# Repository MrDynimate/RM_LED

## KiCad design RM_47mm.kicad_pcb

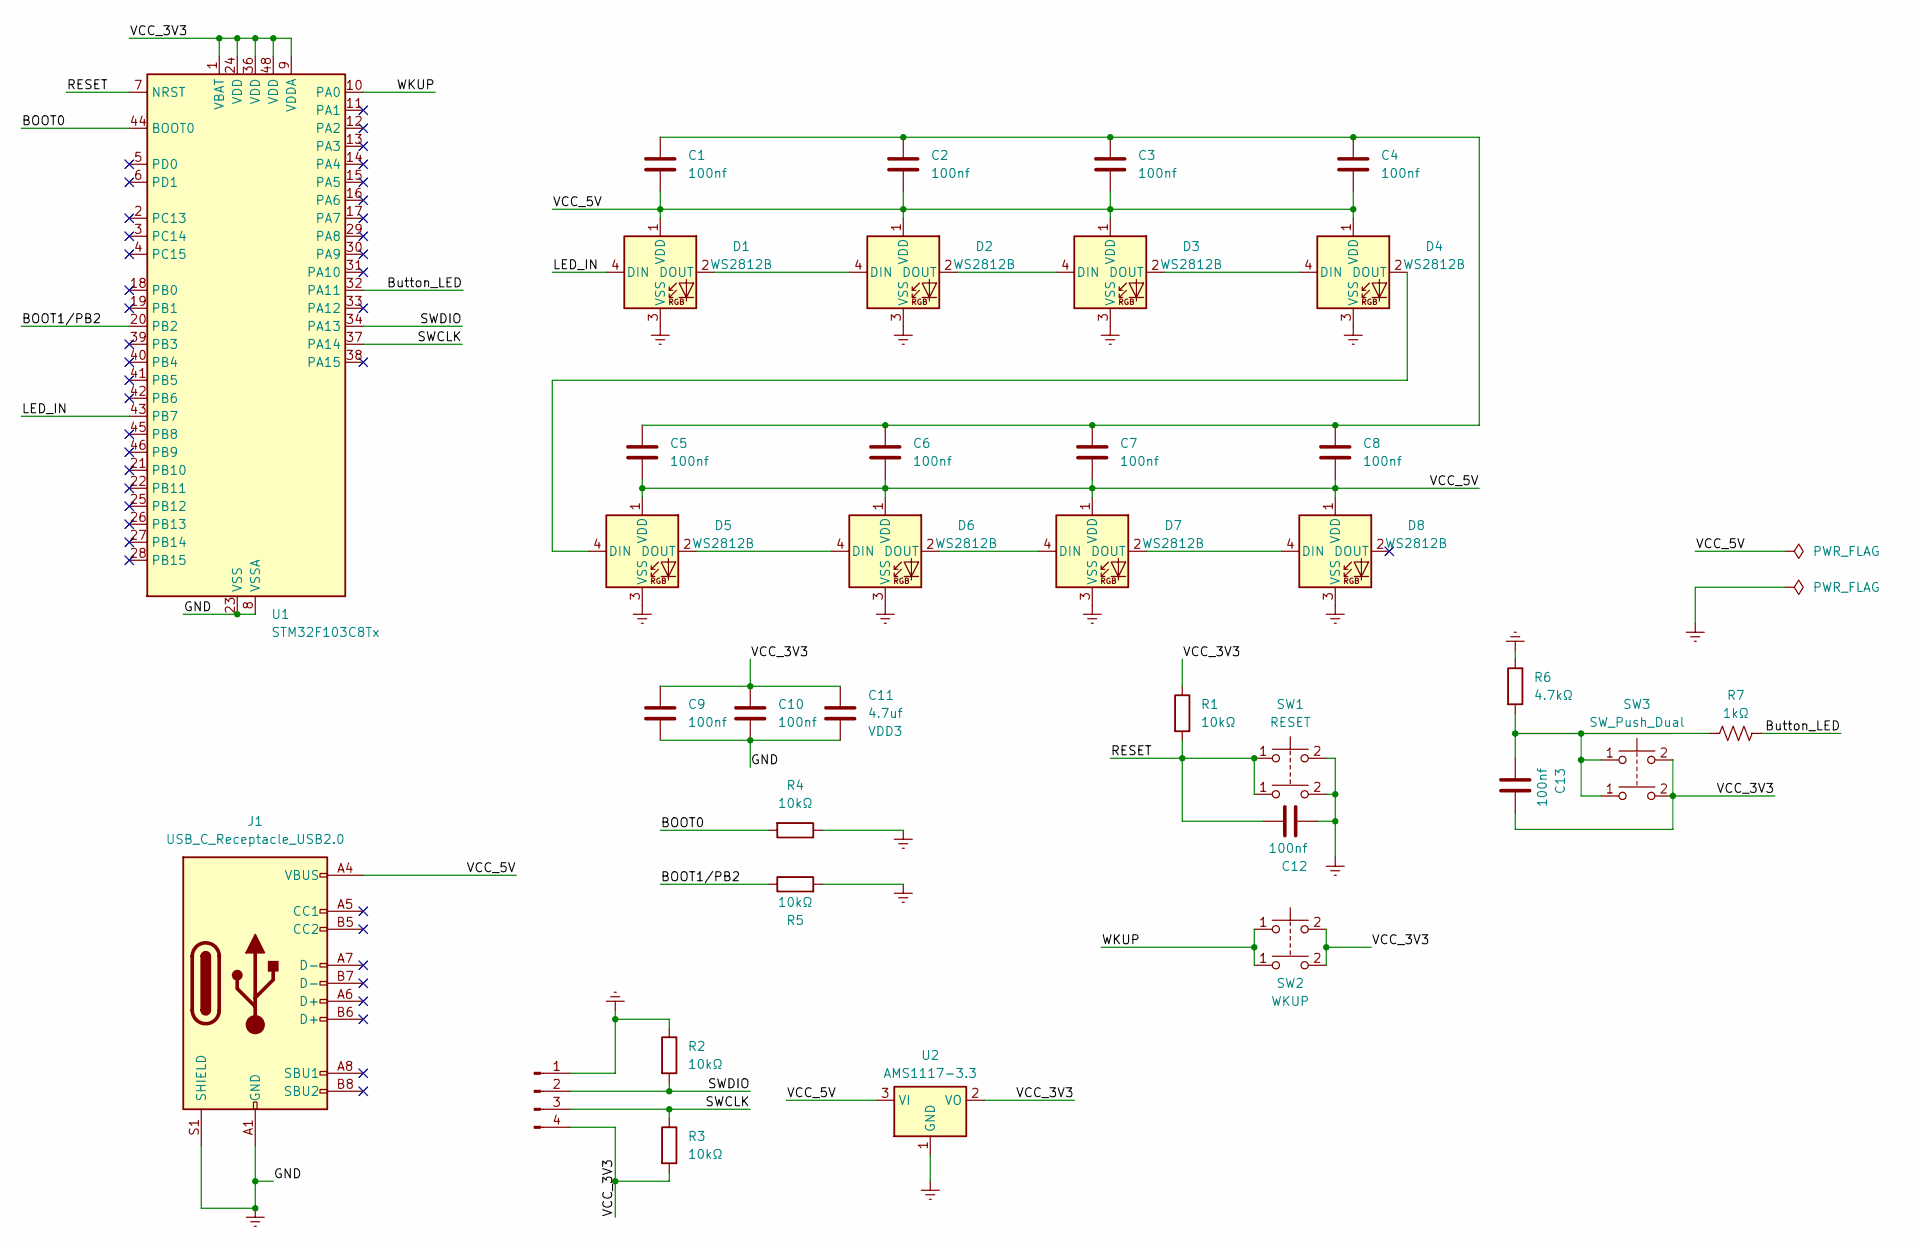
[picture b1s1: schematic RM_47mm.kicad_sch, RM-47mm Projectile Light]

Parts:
C1, C2, C3, C4, C5, C6, C7, C8, C9, C10, C12, C13: 100nf; C_0603_1608Metric
C11: 4.7uf; C_0603_1608Metric
D1, D2, D3, D4, D5, D6, D7, D8: WS2812B; LED_WS2812B_PLCC4_5.0x5.0mm_P3.2mm
J1: USB_C_Receptacle_USB2.0; USB_C_Receptacle_G-Switch_GT-USB-7010ASV
J2: SWD; JST_GH_SM04B-GHS-TB_1x04-1MP_P1.25mm_Horizontal
R1, R2, R3, R4, R5: 10kΩ; R_0603_1608Metric
R6: 4.7kΩ; R_0603_1608Metric
R7: 1kΩ; R_0603_1608Metric
SW1: RESET; SW_Push_1P1T_NO_Vertical_Wuerth_434133025816
SW2: WKUP; SW_Push_1P1T_NO_Vertical_Wuerth_434133025816
SW3: SW_Push_Dual; SW_Tactile_SPST_Angled_PTS645Vx39-2LFS
U1: STM32F103C8Tx; LQFP-48_7x7mm_P0.5mm
U2: AMS1117-3.3; SOT-223-3_TabPin2

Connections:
/BOOT0: R4.2, U1.44 (BOOT0)
/BOOT1/PB2: R5.1, U1.20 (PB2)
/Button_LED: R7.2, U1.32 (PA11)
/LED_IN: D1.4 (DIN), U1.43 (PB7)
/RESET: C12.2, R1.2, SW1.1, U1.7 (NRST)
/SWCLK: J2.3, R3.1, U1.37 (PA14)
/SWDIO: J2.2, R2.2, U1.34 (PA13)
/VCC_3V3: C9.1, C10.1, C11.1, C13.2, J2.4, R1.1, R3.2, SW2.2, SW3.2 (4), U1.1 (VBAT), U1.9 (VDDA), U1.24 (VDD), U1.36 (VDD), U1.48 (VDD), U2.2 (VO)
/VCC_5V: C1.2, C2.2, C3.2, C4.2, C5.2, C6.2, C7.2, C8.2, D1.1 (VDD), D2.1 (VDD), D3.1 (VDD), D4.1 (VDD), D5.1 (VDD), D6.1 (VDD), D7.1 (VDD), D8.1 (VDD), J1.A4 (VBUS), J1.A9 (VBUS), J1.B4 (VBUS), J1.B9 (VBUS), U2.3 (VI)
/WKUP: SW2.1, U1.10 (PA0)
Earth: C9.2, C10.2, C11.2, C12.1, D1.3 (VSS), D2.3 (VSS), D3.3 (VSS), D4.3 (VSS), D5.3 (VSS), D6.3 (VSS), D7.3 (VSS), D8.3 (VSS), J1.A1 (GND), J1.A12 (GND), J1.B1 (GND), J1.B12 (GND), J1.S1 (SHIELD), J2.1, J2.MP, R2.1, R4.1, R5.2, R6.1, SW1.2, U1.8 (VSSA), U1.23 (VSS), U1.35 (VSS), U1.47 (VSS), U2.1 (GND)
unnamed: C1.1, C2.1, C3.1, C4.1, C5.1, C6.1, C7.1, C8.1
unnamed: D1.2 (DOUT), D2.4 (DIN)
unnamed: D2.2 (DOUT), D3.4 (DIN)
unnamed: D3.2 (DOUT), D4.4 (DIN)
unnamed: D4.2 (DOUT), D5.4 (DIN)
unnamed: D5.2 (DOUT), D6.4 (DIN)
unnamed: D6.2 (DOUT), D7.4 (DIN)
unnamed: D7.2 (DOUT), D8.4 (DIN)
unnamed: C13.1, R6.2, R7.1, SW3.1 (3)

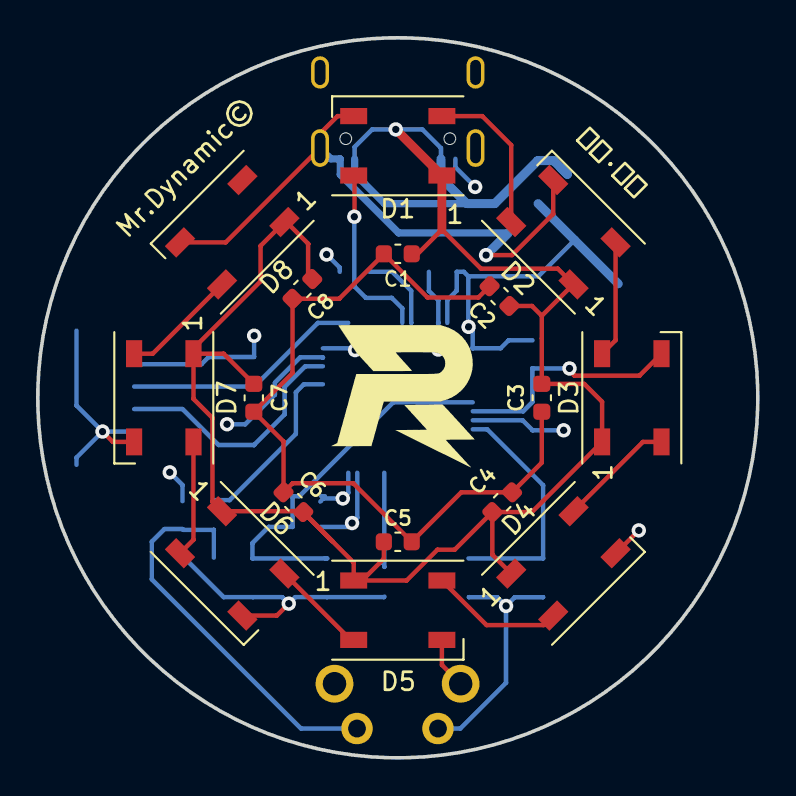
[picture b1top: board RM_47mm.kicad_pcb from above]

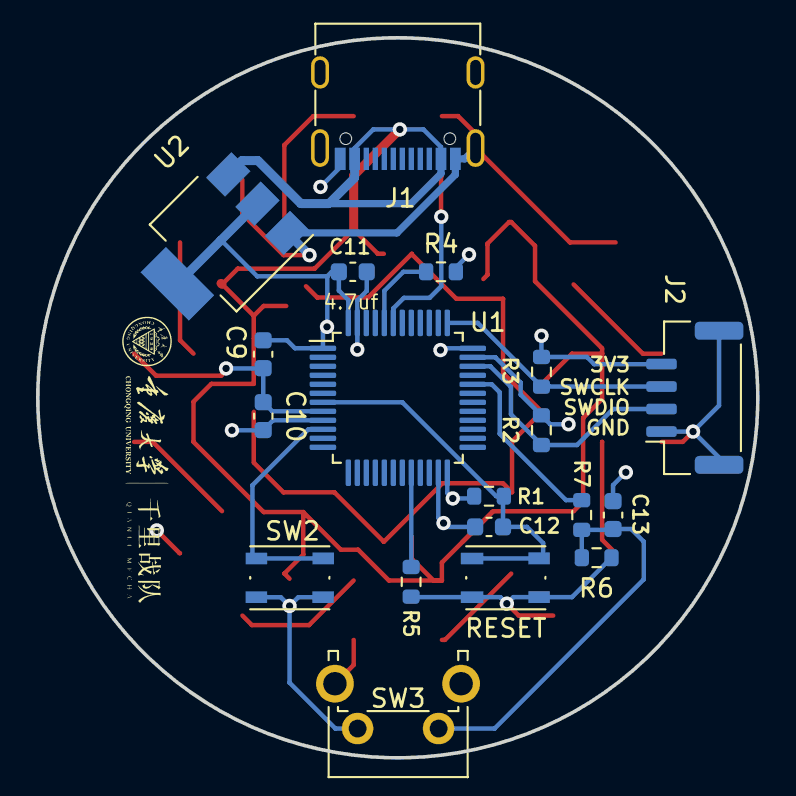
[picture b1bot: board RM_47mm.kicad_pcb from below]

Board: 4 copper layers, 40.0 x 40.0 mm, 35 parts (19 on the bottom side), 20 nets.

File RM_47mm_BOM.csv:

"ID";"指示符";"封装";"数量";"名称";"供应商和参考";
1;"U2";"SOT-223-3_TabPin2";1;"AMS1117-3.3";;;
2;"J1";"USB_C_Receptacle_G-Switch_GT-USB-7010ASV";1;"USB_C_Receptacle_USB2.0";;;
3;"J2";"JST_GH_SM04B-GHS-TB_1x04-1MP_P1.25mm_Horizontal";1;"SWD";;;
4;"R3,R4,R2,R5,R1";"R_0603_1608Metric";5;"10kΩ";;;
5;"D3,D4,D2,D8,D6,D1,D5,D7";"LED_WS2812B_PLCC4_5.0x5.0mm_P3.2mm";8;"WS2812B";;;
6;"C5,C4,C3,C8,C1,C6,C2,C7,C9,C12,C13,C10";"C_0603_1608Metric";12;"100nf";;;
7;"R7";"R_0603_1608Metric";1;"1kΩ";;;
8;"U1";"LQFP-48_7x7mm_P0.5mm";1;"STM32F103C8Tx";;;
9;"SW2";"SW_Push_1P1T_NO_Vertical_Wuerth_434133025816";1;"WKUP";;;
10;"C11";"C_0603_1608Metric";1;"4.7uf";;;
11;"R6";"R_0603_1608Metric";1;"4.7kΩ";;;
12;"SW3";"SW_Tactile_SPST_Angled_PTS645Vx39-2LFS";1;"SW_Push_Dual";;;
13;"SW1";"SW_Push_1P1T_NO_Vertical_Wuerth_434133025816";1;"RESET";;;

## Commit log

2023-09-25 First update
2023-09-25 First uodate
2023-09-25 电路图初版完成
2023-09-26 three
2023-09-30 Four
2023-10-01 Add to 4 Plane & Cancle 网格限制
2023-10-01 连线STEP-1
2023-10-07 Finish All
2023-10-07 Finish All-1
2023-10-08 Manufactor
2023-10-08 Finished
2023-10-08 修改-1
2023-10-08 Final-3
